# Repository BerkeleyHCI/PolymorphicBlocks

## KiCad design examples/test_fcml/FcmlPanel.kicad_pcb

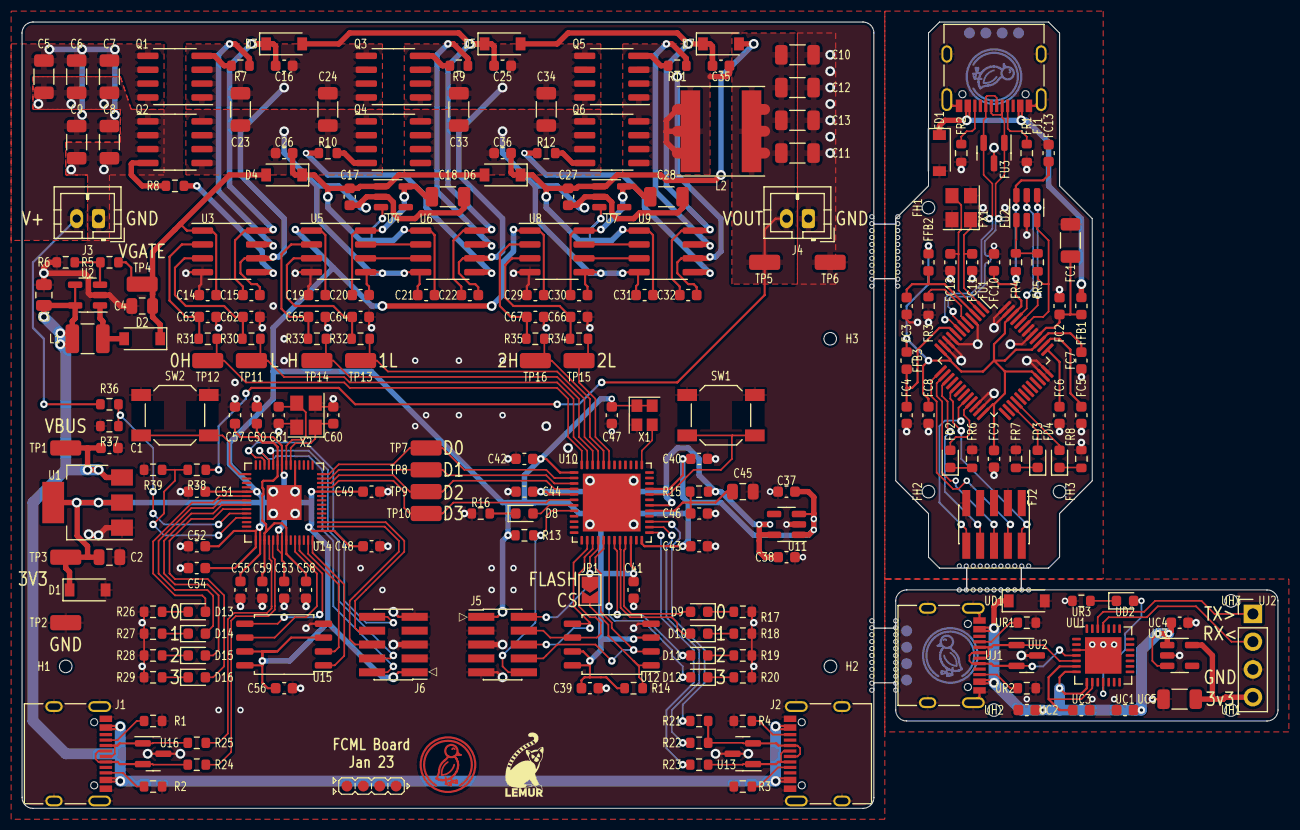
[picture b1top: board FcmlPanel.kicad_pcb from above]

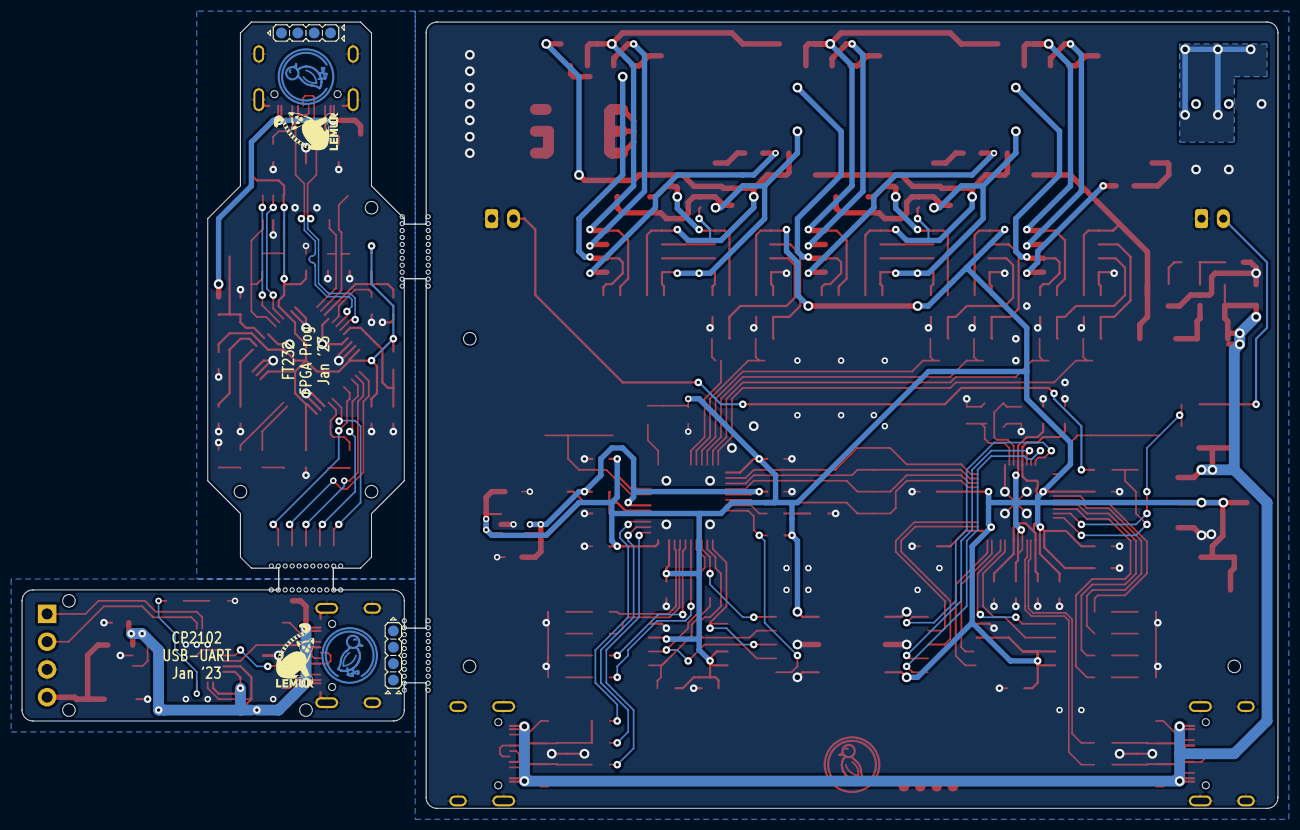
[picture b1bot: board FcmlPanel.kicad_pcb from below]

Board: 2 copper layers, 115.0 x 72.0 mm, 240 parts (6 on the bottom side), 108 nets.

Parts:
C1, C14, C15, C16, C17, C19, C20, C21, C22, C25, C26, C27, C29, C30, C31, C32, C35, C36, C37, C38, C39, C40, C41, C42, C43, C44, C46, C47, C48, C49, C50, C51, C52, C53, C54, C55, C56, C57, C58, C59, C60, C61, C62, C63, C64, C65, C66, C67: C_0603_1608Metric
C2, C3, C4, C45: C_0805_2012Metric
C5, C6, C7, C8, C9, C10, C11, C12, C13, C18, C23, C24, C28, C33, C34: C_1206_3216Metric
D1: BZT52C3V6 (SMC(Sangdest Microelectronicstronic (N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; D_SOD-123
D2: B0520W (Shikues) - 20V 390mV@500mA 500mA SOD-123 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; D_SOD-123
D3, D4, D5, D6, D7: B5819W SL (Changjiang Electronics Tech (CJ)) - 40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; D_SOD-123
D8, D9, D10, D11, D12, D13, D14, D15, D16: KT-0603R (Hubei KENTO Elec) - Red 615~630nm 1.9~2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; LED_0603_1608Metric
FC1: C_1206_3216Metric
FC2, FC3, FC4, FC5, FC6, FC7, FC8, FC9, FC10, FC11, FC12, FC13: C_0603_1608Metric
FD1: MMSZ5232A_R1_00001 (PANJIT International) - 5?A@3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; D_SOD-123
FD2: C2290 (Hubei KENTO Elec) - White 0603 Light Emitt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; LED_0603_1608Metric
FD3, FD4: LED_0603_1608Metric
FFB1, FFB2, FFB3: L_0603_1608Metric
FH1, FH2, FH3: JlcToolingHole_1.152mm
FJ1: COM-15111 (Sparkfun); USB_C_Receptacle_XKB_U262-16XN-4BVC11
FJ2: PinHeader1.27 Shrouded 2x5 (Generic); PinHeader_2x05_P1.27mm_Vertical_SMD
FR1, FR2, FR3, FR4, FR5, FR6, FR7, FR8: R_0603_1608Metric
FU1: FT232HL (FTDI, Future Technology Devices Internat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; LQFP-48_7x7mm_P0.5mm
FU2: 93LC56B (Microchip Technology); SOT-23-6
FU3: PGB102ST23 (Littelfuse); SOT-23
FU4: Duck; Symbol_Duckling
FU5: Lemur; Symbol_LemurSmall
FU6: IdDots4; Indicator_IdDots_4
FX1: Crystal_SMD_3225-4Pin_3.2x2.5mm
H1, H2, H3: JlcToolingHole_1.152mm
J1, J2: COM-15111 (Sparkfun); USB_C_Receptacle_XKB_U262-16XN-4BVC11
J3, J4: B2B-PH-K (JST); JST_PH_B2B-PH-K_1x02_P2.00mm_Vertical
J5, J6: PinHeader1.27 Shrouded 2x5 (Generic); PinHeader_2x05_P1.27mm_Vertical_SMD
JP1: SolderJumper-2_P1.3mm_Open_TrianglePad1.0x1.5mm
L1: L_1210_3225Metric
L2: L_Taiyo-Yuden_NR-80xx
Q1, Q2, Q3, Q4, Q5, Q6: HSM4410 (HUASHUO) - 30V 12A 2.5W 9.5m?@10V,12A 2.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; SOIC-8_3.9x4.9mm_P1.27mm
R1, R2, R3, R4, R5, R6, R7, R8, R9, R10, R11, R12, R13, R14, R15, R16, R17, R18, R19, R20, R21, R22, R23, R24, R25, R26, R27, R28, R29, R30, R31, R32, R33, R34, R35, R36, R37, R38, R39: R_0603_1608Metric
SW1, SW2: 5.1mm switch; SW_SPST_SKQG_WithoutStem
TP1: 5015 (Keystone) - vusb; TestPoint_TE_RCT_0805
TP2, TP6: 5015 (Keystone) - gnd; TestPoint_TE_RCT_0805
TP3: 5015 (Keystone) - v3v3; TestPoint_TE_RCT_0805
TP4: 5015 (Keystone) - vgate; TestPoint_TE_RCT_0805
TP5: 5015 (Keystone) - _conv_pwr_out_link; TestPoint_TE_RCT_0805
TP7: 5015 (Keystone) - _mcu_gpio_fpga0_link; TestPoint_TE_RCT_0805
TP8: 5015 (Keystone) - _mcu_gpio_fpga1_link; TestPoint_TE_RCT_0805
TP9: 5015 (Keystone) - _mcu_gpio_fpga2_link; TestPoint_TE_RCT_0805
TP10: 5015 (Keystone) - _mcu_gpio_fpga3_link; TestPoint_TE_RCT_0805
TP11: 5015 (Keystone) - _fpga_gpio_pwm_link.0L; TestPoint_TE_RCT_0805
TP12: 5015 (Keystone) - _fpga_gpio_pwm_link.0H; TestPoint_TE_RCT_0805
TP13: 5015 (Keystone) - _fpga_gpio_pwm_link.1L; TestPoint_TE_RCT_0805
TP14: 5015 (Keystone) - _fpga_gpio_pwm_link.1H; TestPoint_TE_RCT_0805
TP15: 5015 (Keystone) - _fpga_gpio_pwm_link.2L; TestPoint_TE_RCT_0805
TP16: 5015 (Keystone) - _fpga_gpio_pwm_link.2H; TestPoint_TE_RCT_0805
U1: LD1117S33TR (STMicroelectronics); SOT-223-3_TabPin2
U2: AP3012K (Diodes Incorporated); SOT-23-5
U3, U6, U9: IR2301 (Infineon Technologies); SOIC-8_3.9x4.9mm_P1.27mm
U4, U7: AP2204K-3.3 (Diodes Incorporated); SOT-23-5
U5, U8: CBMuD1200L (Corebai); SOIC-8_3.9x4.9mm_P1.27mm
U10: ICE40UP5K-SG48 (Lattice Semiconductor Corporation); QFN-48-1EP_7x7mm_P0.5mm_EP5.3x5.3mm
U11: LP5907MFX-1.2/NOPB (Texas Instruments); SOT-23-5
U12, U15: W25Q128JVSIQ (Winbond Electronics); SOIC-8_5.23x5.23mm_P1.27mm
U13, U16: PGB102ST23 (Littelfuse); SOT-23
U14: RP2040 (Raspberry Pi); QFN-56-1EP_7x7mm_P0.4mm_EP3.2x3.2mm
U17: Duck; Symbol_Duckling
U18: Lemur; Symbol_LemurSmall
U19: IdDots4; Indicator_IdDots_4
UC1, UC2, UC3, UC4: C_0603_1608Metric
UC5: C_1206_3216Metric
UD1: MMSZ5232A_R1_00001 (PANJIT International) - 5?A@3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; D_SOD-123
UD2: C2290 (Hubei KENTO Elec) - White 0603 Light Emitt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; LED_0603_1608Metric
UH1, UH2, UH3: JlcToolingHole_1.152mm
UJ1: COM-15111 (Sparkfun); USB_C_Receptacle_XKB_U262-16XN-4BVC11
UJ2: PinHeader2.54 1x4 (Generic); PinHeader_1x04_P2.54mm_Vertical
UR1, UR2, UR3: R_0603_1608Metric
UU1: CP2102 (Silicon Labs); QFN-28-1EP_5x5mm_P0.5mm_EP3.35x3.35mm
UU2: PGB102ST23 (Littelfuse); SOT-23
UU3: AP2204K-3.3 (Diodes Incorporated); SOT-23-5
UU4: Duck; Symbol_Duckling
UU5: Lemur; Symbol_LemurSmall
UU6: IdDots4; Indicator_IdDots_4
X1: Crystal_SMD_2520-4Pin_2.5x2.0mm
X2: Crystal_SMD_3225-4Pin_3.2x2.5mm

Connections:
cdone.res.a: D8.1, R16.1
conv.pwr_in: C5.1, C6.1, C7.1, C8.1, C9.1, J3.2, Q1.5, Q1.6, Q1.7, Q1.8, R36.1
conv.pwr_out: C10.1, C11.1, C12.1, C13.1, J4.2, L2.2, R38.1, TP5.1
conv.sw[0].high_boot_cap.pos: C15.1, C16.1, D3.1, U3.8
conv.sw[0].high_gate_res.a: R7.1, U3.7
conv.sw[0].high_gate_res.b: Q1.4, R7.2
conv.sw[0].low_gate_res.a: R8.1, U3.5
conv.sw[0].low_gate_res.b: Q2.4, R8.2
conv.sw[1].driver.high_in: U5.7, U6.2
conv.sw[1].driver.low_in: U5.6, U6.3
conv.sw[1].high_boot_out: C22.1, C25.1, D3.2, D5.1, U6.8
conv.sw[1].high_gate_res.a: R9.1, U6.7
conv.sw[1].high_gate_res.b: Q3.4, R9.2
conv.sw[1].high_in: C15.2, C16.2, C23.1, C24.1, Q1.1, Q1.2, Q1.3, Q3.5, Q3.6, Q3.7, Q3.8, U3.6
conv.sw[1].iso.pwr_b: C18.1, C20.1, U4.5, U5.8
conv.sw[1].low_gate_res.a: R10.1, U6.5
conv.sw[1].low_gate_res.b: Q4.4, R10.2
conv.sw[1].low_in: C17.2, C18.2, C20.2, C21.2, C23.2, C24.2, C26.2, Q2.5, Q2.6, Q2.7, Q2.8, Q4.1, Q4.2, Q4.3, U4.2, U5.5, U6.4
conv.sw[2].driver.high_in: U8.7, U9.2
conv.sw[2].driver.low_in: U8.6, U9.3
conv.sw[2].high_boot_out: C32.1, C35.1, D5.2, D7.1, U9.8
conv.sw[2].high_gate_res.a: R11.1, U9.7
conv.sw[2].high_gate_res.b: Q5.4, R11.2
conv.sw[2].high_in: C22.2, C25.2, C33.1, C34.1, Q3.1, Q3.2, Q3.3, Q5.5, Q5.6, Q5.7, Q5.8, U6.6
conv.sw[2].iso.pwr_b: C28.1, C30.1, U7.5, U8.8
conv.sw[2].low_boot_in: C17.1, C21.1, C26.1, D4.1, D6.2, U4.1, U4.3, U6.1
conv.sw[2].low_boot_out: C27.1, C31.1, C36.1, D6.1, D7.2, U7.1, U7.3, U9.1
conv.sw[2].low_gate_res.a: R12.1, U9.5
conv.sw[2].low_gate_res.b: Q6.4, R12.2
conv.sw[2].low_in: C27.2, C28.2, C30.2, C31.2, C33.2, C34.2, C36.2, Q4.5, Q4.6, Q4.7, Q4.8, Q6.1, Q6.2, Q6.3, U7.2, U8.5, U9.4
conv.sw[2].low_out: C32.2, C35.2, L2.1, Q5.1, Q5.2, Q5.3, Q6.5, Q6.6, Q6.7, Q6.8, U9.6
conv_in_sense.output: R36.2, R37.1, U14.38
conv_out_sense.output: R38.2, R39.1, U14.39
fpga.cdone: D8.2, U10.7
fpga.cs_jmp.output: JP1.2, R14.2, U12.1
fpga.gpio.led_0: D9.2, U10.21
fpga.gpio.led_1: D10.2, U10.20
fpga.gpio.led_2: D11.2, U10.19
fpga.gpio.led_3: D12.2, U10.18
fpga.gpio.pwm_0H: R31.1, TP12.1, U10.48
fpga.gpio.pwm_0L: R30.1, TP11.1, U10.47
fpga.gpio.pwm_1H: R33.1, TP14.1, U10.46
fpga.gpio.pwm_1L: R32.1, TP13.1, U10.45
fpga.gpio.pwm_2H: R35.1, TP16.1, U10.44
fpga.gpio.pwm_2L: R34.1, TP15.1, U10.43
fpga.ic.creset_b: J5.10, R13.2, U10.8
fpga.ic.spi_config.miso: J5.8, U10.17, U12.2
fpga.ic.spi_config.mosi: J5.6, U10.14, U12.5
fpga.ic.spi_config.sck: J5.4, U10.15, U12.6
fpga.ic.spi_config_cs: J5.2, JP1.1, U10.16
fpga.pll_res.pwr_out: C45.1, C46.1, R15.2, U10.29
fpga.vcc_reg.pwr_out: C38.1, C44.1, R15.1, U10.5, U10.30, U11.5
fpga_led.led[0].res.a: D9.1, R17.1
fpga_led.led[1].res.a: D10.1, R18.1
fpga_led.led[2].res.a: D11.1, R19.1
fpga_led.led[3].res.a: D12.1, R20.1
fpga_osc.out: U10.37, X1.3
fpga_sw.out: SW1.2, U10.32
gnd: C1.2, C2.2, C3.2, C4.2, C5.2, C6.2, C7.2, C8.2, C9.2, C10.2, C11.2, C12.2, C13.2, C14.2, C19.2, C29.2, C37.2, C38.2, C39.2, C40.2, C41.2, C42.2, C43.2, C44.2, C45.2, C46.2, C47.2, C48.2, C49.2, C50.2, C51.2, C52.2, C53.2, C54.2, C55.2, C56.2, C57.2, C58.2, C59.2, C60.2, C61.2, C62.2, C63.2, C64.2, C65.2, C66.2, C67.2, D1.2, FC1.2, FC2.2, FC3.2, FC4.2, FC5.2, FC6.2, FC7.2, FC8.2, FC9.2, FC10.2, FC11.2, FC12.2, FC13.2, FD1.2, FJ1.A1, FJ1.A12, FJ1.B1, FJ1.B12, FJ1.S1, FJ2.3, FJ2.5, FJ2.9, FR1.1, FR2.1, FR3.2, FR6.2, FR7.2, FR8.2, FU1.4, FU1.9, FU1.10, FU1.11, FU1.22, FU1.23, FU1.35, FU1.36, FU1.41, FU1.42, FU1.47, FU1.48, FU2.2, FU3.3, FX1.2, FX1.4, J1.A1, J1.A12, J1.B1, J1.B12, J1.S1, J2.A1, J2.A12, J2.B1, J2.B12, J2.S1, J3.1, J4.1, J5.3, J5.5, J5.9, J6.3, J6.5, J6.9, Q2.1, Q2.2, Q2.3, R1.1, R2.1, R3.1, R4.1, R6.2, R16.2, R17.2, R18.2, R19.2, R20.2, R26.2, R27.2, R28.2, R29.2, R37.2, R39.2, SW1.1, SW2.1, TP2.1, TP6.1, U1.1, U2.2, U3.4, U5.4, U8.4, U10.49, U11.2, U12.4, U13.3, U14.19, U14.57, U15.4, U16.3, UC1.2, UC2.2, UC3.2, UC4.2, UC5.2, UD1.2, UJ1.A1, UJ1.A12, UJ1.B1, UJ1.B12, UJ1.S1, UJ2.3, UR1.1, UR2.1, UR3.2, UU1.3, UU1.29, UU2.3, UU3.2, X1.2, X2.2, X2.4
mcu.crystal.crystal.a: C60.1, U14.20, X2.1
mcu.crystal.crystal.b: C61.1, U14.21, X2.3
mcu.gpio.led_0: D13.2, U14.34
mcu.gpio.led_1: D14.2, U14.35
mcu.gpio.led_2: D15.2, U14.36
mcu.gpio.led_3: D16.2, U14.37
mcu.ic.qspi.miso: U14.55, U15.2
mcu.ic.qspi.mosi: U14.53, U15.5
mcu.ic.qspi.sck: U14.52, U15.6
mcu.ic.qspi_cs: U14.56, U15.1
mcu.ic.vreg_vout: C57.1, C58.1, C59.1, U14.23, U14.45, U14.50
mcu.swd.swd.reset: J6.10, U14.26
mcu.swd.swd.swclk: J6.4, U14.24
mcu.swd.swd.swdio: J6.2, U14.25
mcu.swd.swo: J6.6, U14.2
mcu.swd.tdi: J6.8, U14.3
mcu.usb_chain_0.d_N: R25.1, U14.46
mcu.usb_chain_0.d_P: R24.1, U14.47
mcu_leds.led[0].res.a: D13.1, R26.1
mcu_leds.led[1].res.a: D14.1, R27.1
mcu_leds.led[2].res.a: D15.1, R28.1
mcu_leds.led[3].res.a: D16.1, R29.1
mcu_sw.out: SW2.2, U14.29
reg_vgate.fb.output: R5.2, R6.1, U2.3
reg_vgate.power_path.switch: D2.2, L1.2, U2.1
tp_fpga[0].io: TP7.1, U10.2, U14.14
tp_fpga[1].io: TP8.1, U10.3, U14.13
tp_fpga[2].io: TP9.1, U10.4, U14.12
tp_fpga[3].io: TP10.1, U10.6, U14.11
tp_pwm.output.0H: C63.1, R31.2, U3.2
tp_pwm.output.0L: C62.1, R30.2, U3.3
tp_pwm.output.1H: C65.1, R33.2, U5.2
tp_pwm.output.1L: C64.1, R32.2, U5.3
tp_pwm.output.2H: C67.1, R35.2, U8.2
tp_pwm.output.2L: C66.1, R34.2, U8.3
usb_fpga.conn.A5: J2.A5, R3.2
usb_fpga.conn.B5: J2.B5, R4.2
usb_fpga_bitbang.dm: R23.1, U10.25
usb_fpga_bitbang.dp: R22.1, U10.26
usb_fpga_bitbang.dp_pull: R21.1, U10.27
usb_fpga_chain_0.d_N: J2.A7, J2.B7, R23.2, U13.1
usb_fpga_chain_0.d_P: J2.A6, J2.B6, R21.2, R22.2, U13.2
usb_mcu.conn.A5: J1.A5, R1.2
usb_mcu.conn.B5: J1.B5, R2.2
usb_mcu_chain_0.d_N: J1.A7, J1.B7, R25.2, U16.1
usb_mcu_chain_0.d_P: J1.A6, J1.B6, R24.2, U16.2
v3v3: C2.1, C19.1, C29.1, C37.1, C39.1, C40.1, C41.1, C42.1, C43.1, C47.1, C48.1, C49.1, C50.1, C51.1, C52.1, C53.1, C54.1, C55.1, C56.1, D1.1, J5.1, J6.1, R13.1, R14.1, TP3.1, U1.2, U5.1, U8.1, U10.1, U10.22, U10.24, U10.33, U11.1, U11.3, U12.3, U12.7, U12.8, U14.1, U14.10, U14.22, U14.33, U14.42, U14.43, U14.44, U14.48, U14.49, U15.3, U15.7, U15.8, UC5.1, UJ2.4, UU3.5, X1.1, X1.4
vgate: C4.1, C14.1, D2.1, D4.2, R5.1, TP4.1, U3.1
vusb: C1.1, C3.1, FD1.1, FFB1.1, FJ1.A4, FJ1.A9, FJ1.B4, FJ1.B9, J1.A4, J1.A9, J1.B4, J1.B9, J2.A4, J2.A9, J2.B4, J2.B9, L1.1, TP1.1, U1.3, U2.4, U2.5, UC1.1, UC2.1, UC4.1, UD1.1, UJ1.A4, UJ1.A9, UJ1.B4, UJ1.B9, UU1.7, UU1.8, UU3.1, UU3.3

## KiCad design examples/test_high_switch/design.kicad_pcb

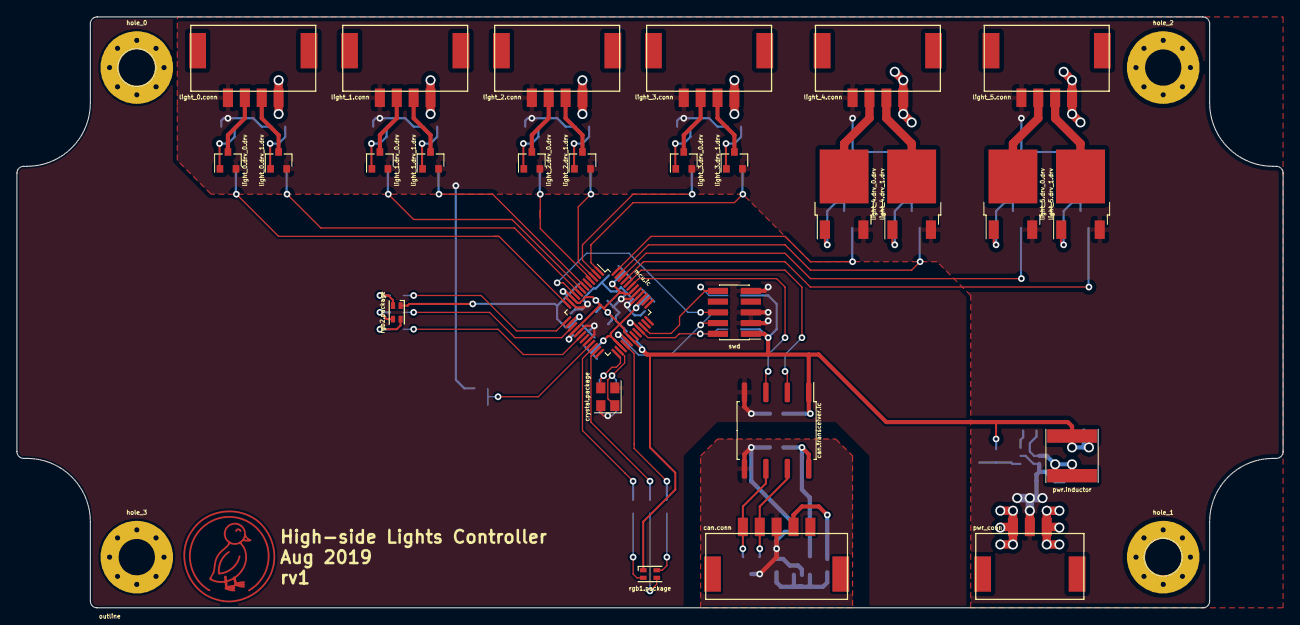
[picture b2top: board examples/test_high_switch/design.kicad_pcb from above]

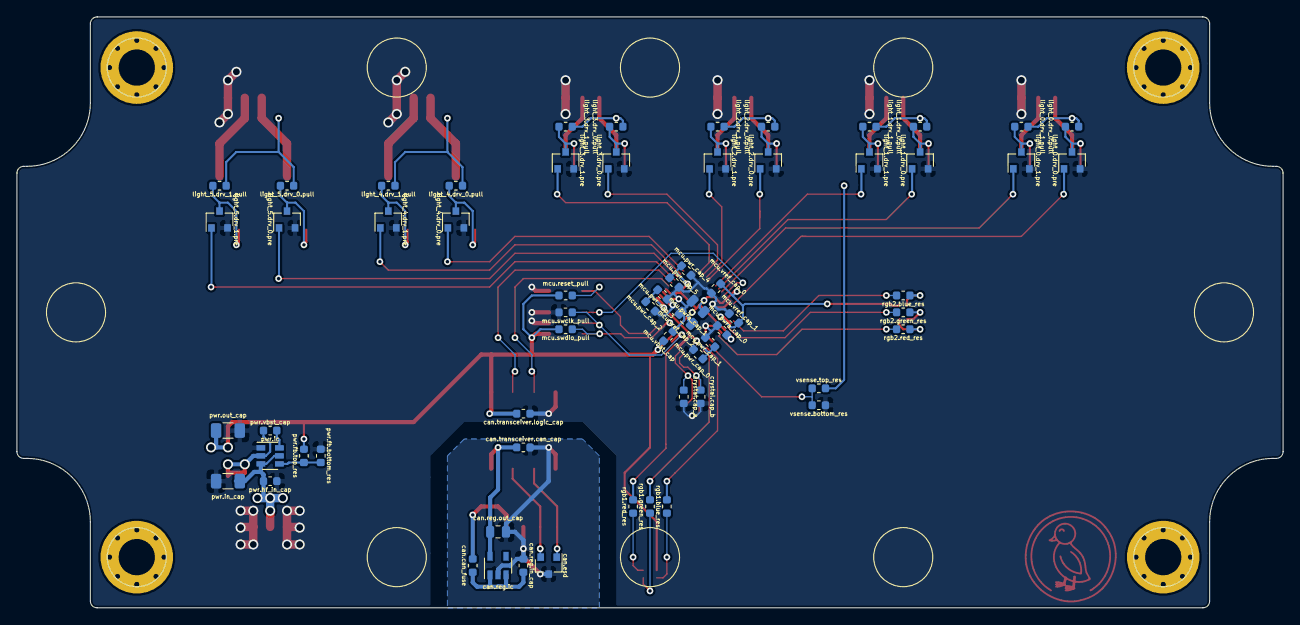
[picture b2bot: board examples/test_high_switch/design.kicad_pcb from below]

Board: 2 copper layers, 150.0 x 70.0 mm, 96 parts (63 on the bottom side), 69 nets.

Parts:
can.can_fuse: 0ZCM0005FF2G; R_0603_1608Metric
can.conn: Duraclik; Molex_DuraClik_vert_5pin
can.esd: PESD1CAN,215; SOT-23
can.reg.ic: AP2204K-5.0; SOT-23-5
can.reg.in_cap: 1µF, 25V, CL10A105KA8NNNC (C=(8.8e-07, 1.32e-06) 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; C_0603_1608Metric
can.reg.out_cap: 2.2µF, 10V, CL21B225KPFNNNE (C=(1.76e-06, 2.64e-0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; C_0805_2012Metric
can.transceiver.can_cap, can.transceiver.logic_cap: 0.1µF, 50V, CL10B104KB8NNNC (C=(8e-08, 1.2e-07) F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; C_0603_1608Metric
can.transceiver.ic: ISO1050DUB; SOP-8_6.62x9.15mm_P2.54mm
crystal.cap_a, crystal.cap_b: 18pF, 50V, CL10C180FB8NNNC (C=(1.764e-11, 1.836e-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; C_0603_1608Metric
crystal.package: 7V-12.000MAHE-T; Oscillator_SMD_Abracon_ASE-4Pin_3.2x2.5mm
duck: Duck; Duckling
hole_0, hole_1, hole_2, hole_3: M4; MountingHole_4.3mm_M4_Pad_Via
light_0.conn, light_1.conn, light_2.conn, light_3.conn, light_4.conn, light_5.conn: Duraclik; Molex_DuraClik_vert_4pin
light_0.drv_0.drv, light_0.drv_1.drv, light_1.drv_0.drv, light_1.drv_1.drv, light_2.drv_0.drv, light_2.drv_1.drv, light_3.drv_0.drv, light_3.drv_1.drv: DMP3099L-7 (Vds=(10.8, 13.200000000000001) V, Ids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; SOT-23
light_0.drv_0.pre, light_0.drv_1.pre, light_1.drv_0.pre, light_1.drv_1.pre, light_2.drv_0.pre, light_2.drv_1.pre, light_3.drv_0.pre, light_3.drv_1.pre, light_4.drv_0.pre, light_4.drv_1.pre, light_5.drv_0.pre, light_5.drv_1.pre: NX138AKR (Vds=(10.8, 13.200000000000001) V, Ids=(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; SOT-23
light_0.drv_0.pull, light_0.drv_1.pull, light_1.drv_0.pull, light_1.drv_1.pull, light_2.drv_0.pull, light_2.drv_1.pull, light_3.drv_0.pull, light_3.drv_1.pull, light_4.drv_0.pull, light_4.drv_1.pull, light_5.drv_0.pull, light_5.drv_1.pull: 10000, 1%, 0.1W (R=(9900.0, 10100.0) Ohm, P=(0.0,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; R_0603_1608Metric
light_4.drv_0.drv, light_4.drv_1.drv, light_5.drv_0.drv, light_5.drv_1.drv: TSM7P06CP ROG (Vds=(10.8, 13.200000000000001) V, 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; TO-252-2
mcu.ic: LPC1549JBD48; LQFP-48_7x7mm_P0.5mm
mcu.pwr_cap_0, mcu.pwr_cap_2, mcu.pwr_cap_4, mcu.pwra_cap_0, mcu.vbat_cap, mcu.vref_cap_0, mcu.vref_cap_1: 0.1µF, 50V, CL10B104KB8NNNC (C=(8e-08, 1.2e-07) F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; C_0603_1608Metric
mcu.pwr_cap_1, mcu.pwr_cap_3, mcu.pwr_cap_5: 10000pF, 50V, CL10B103KB8NNNC (C=(8e-09, 1.2e-08)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; C_0603_1608Metric
mcu.pwra_cap_1, mcu.vref_cap_2: 10µF, 10V, CL21A106KPFNNNG (C=(8e-06, 1.199999999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; C_0805_2012Metric
mcu.reset_pull: 10000, 1%, 0.1W (R=(9500.0, 10500.0) Ohm, P=(0.0,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; R_0603_1608Metric
mcu.swclk_pull, mcu.swdio_pull: 10000, 1%, 0.1W (R=(9500.0, 105000.0) Ohm, P=(0.0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; R_0603_1608Metric
outline: PN1332_Panel; Outline_150mm_70mm_PNX-91432
pwr.fb.bottom_res: 10000, 1%, 0.1W (R=(9900.0, 10100.0) Ohm, P=(0.0,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; R_0603_1608Metric
pwr.fb.top_res: 33000, 1%, 0.1W (R=(32670.0, 33330.0) Ohm, P=(0.0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; R_0603_1608Metric
pwr.hf_in_cap, pwr.vbst_cap: 0.1µF, 50V, CL10B104KB8NNNC (C=(8e-08, 1.2e-07) F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; C_0603_1608Metric
pwr.ic: TPS561201; SOT-23-6
pwr.in_cap: 22µF, 16V, CL31A226MOCLNNC (C=(7.498403575989784e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; C_1206_3216Metric
pwr.inductor: 10µH, 2.5A, NR6045T100M (L=(4.6396372126436784e-0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; L_Taiyo-Yuden_NR-60xx
pwr.out_cap: 22µF, 6.3V, CL31A226MQHNNNE (C=(1.034482758620689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; C_1206_3216Metric
pwr_conn: Duraclik; Molex_DuraClik_vert_3pin
rgb1.blue_res, rgb1.green_res, rgb1.red_res, rgb2.blue_res, rgb2.green_res, rgb2.red_res: 1000, 1%, 0.1W (R=(950.0, 1050.0) Ohm, P=(0.0, 0.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; R_0603_1608Metric
rgb1.package, rgb2.package: LED_RGB_0606
swd: SWD; PinHeader_2x05_P1.27mm_Vertical_SMD
vsense.bottom_res: 1500, 1%, 0.1W (R=(1485.0, 1515.0) Ohm, P=(0.0, 0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; R_0603_1608Metric
vsense.top_res: 4700, 1%, 0.1W (R=(4653.0, 4747.0) Ohm, P=(0.0, 0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; R_0603_1608Metric

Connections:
can.can.canh: can.conn.4, can.esd.2, can.transceiver.ic.7
can.can.canl: can.conn.5, can.esd.1, can.transceiver.ic.6
can.can_gnd: can.conn.3, can.esd.3, can.reg.ic.2, can.reg.in_cap.2, can.reg.out_cap.2, can.transceiver.can_cap.2, can.transceiver.ic.5
can.can_pwr: can.can_fuse.1, can.conn.2
can.controller.txd: can.transceiver.ic.3, mcu.ic.43
can.reg.pwr_in: can.can_fuse.2, can.reg.ic.1, can.reg.ic.3, can.reg.in_cap.1
can.reg.pwr_out: can.reg.ic.5, can.reg.out_cap.1, can.transceiver.can_cap.1, can.transceiver.ic.8
crystal.crystal.b: crystal.cap_b.1, crystal.package.3, mcu.ic.25
gnd: can.transceiver.ic.4, can.transceiver.logic_cap.2, crystal.cap_a.2, crystal.cap_b.2, crystal.package.2, crystal.package.4, light_0.conn.4, light_0.drv_0.pre.2, light_0.drv_1.pre.2, light_1.conn.4, light_1.drv_0.pre.2, light_1.drv_1.pre.2, light_2.conn.4, light_2.drv_0.pre.2, light_2.drv_1.pre.2, light_3.conn.4, light_3.drv_0.pre.2, light_3.drv_1.pre.2, light_4.conn.4, light_4.drv_0.pre.2, light_4.drv_1.pre.2, light_5.conn.4, light_5.drv_0.pre.2, light_5.drv_1.pre.2, mcu.ic.11, mcu.ic.17, mcu.ic.20, mcu.ic.40, mcu.ic.41, mcu.pwr_cap_0.2, mcu.pwr_cap_1.2, mcu.pwr_cap_2.2, mcu.pwr_cap_3.2, mcu.pwr_cap_4.2, mcu.pwr_cap_5.2, mcu.pwra_cap_0.2, mcu.pwra_cap_1.2, mcu.swclk_pull.1, mcu.vbat_cap.2, mcu.vref_cap_0.2, mcu.vref_cap_1.2, mcu.vref_cap_2.2, pwr.fb.bottom_res.2, pwr.hf_in_cap.2, pwr.ic.1, pwr.in_cap.2, pwr.out_cap.2, pwr_conn.1, pwr_conn.3, swd.3, swd.5, swd.9, vsense.bottom_res.2
light_0.conn.out_0: light_0.conn.2, light_0.drv_0.drv.3
light_0.control_0: light_0.drv_0.pre.1, mcu.ic.12
light_0.drv_0.drv.gate: light_0.drv_0.drv.1, light_0.drv_0.pre.3, light_0.drv_0.pull.2
light_0.drv_1.output: light_0.conn.3, light_0.drv_1.drv.3
light_0.drv_1.pull.2: light_0.drv_1.drv.1, light_0.drv_1.pre.3, light_0.drv_1.pull.2
light_1.conn.out_0: light_1.conn.2, light_1.drv_0.drv.3
light_1.conn.out_1: light_1.conn.3, light_1.drv_1.drv.3
light_1.control_0: light_1.drv_0.pre.1, mcu.ic.7
light_1.drv_0.drv.gate: light_1.drv_0.drv.1, light_1.drv_0.pre.3, light_1.drv_0.pull.2
light_1.drv_1.drv.1: light_1.drv_1.drv.1, light_1.drv_1.pre.3, light_1.drv_1.pull.2
light_2.conn.out_1: light_2.conn.3, light_2.drv_1.drv.3
light_2.control_1: light_2.drv_1.pre.1, mcu.ic.3
light_2.drv_0.output: light_2.conn.2, light_2.drv_0.drv.3
light_2.drv_0.pull.2: light_2.drv_0.drv.1, light_2.drv_0.pre.3, light_2.drv_0.pull.2
light_2.drv_1.drv.gate: light_2.drv_1.drv.1, light_2.drv_1.pre.3, light_2.drv_1.pull.2
light_3.conn.3: light_3.conn.3, light_3.drv_1.drv.3
light_3.drv_0.output: light_3.conn.2, light_3.drv_0.drv.3
light_3.drv_0.pre.drain: light_3.drv_0.drv.1, light_3.drv_0.pre.3, light_3.drv_0.pull.2
light_3.drv_1.drv.1: light_3.drv_1.drv.1, light_3.drv_1.pre.3, light_3.drv_1.pull.2
light_4.conn.out_1: light_4.conn.3, light_4.drv_1.drv.2
light_4.control_0: light_4.drv_0.pre.1, mcu.ic.48
light_4.drv_0.drv.gate: light_4.drv_0.drv.1, light_4.drv_0.pre.3, light_4.drv_0.pull.2
light_4.drv_0.output: light_4.conn.2, light_4.drv_0.drv.2
light_4.drv_1.drv.1: light_4.drv_1.drv.1, light_4.drv_1.pre.3, light_4.drv_1.pull.2
light_5.conn.2: light_5.conn.2, light_5.drv_0.drv.2
light_5.conn.out_1: light_5.conn.3, light_5.drv_1.drv.2
light_5.control_0: light_5.drv_0.pre.1, mcu.ic.46
light_5.control_1: light_5.drv_1.pre.1, mcu.ic.45
light_5.drv_0.pull.b: light_5.drv_0.drv.1, light_5.drv_0.pre.3, light_5.drv_0.pull.2
light_5.drv_1.pre.3: light_5.drv_1.drv.1, light_5.drv_1.pre.3, light_5.drv_1.pull.2
mcu.can_0.rxd: can.transceiver.ic.2, mcu.ic.44
mcu.digital_4: light_4.drv_1.pre.1, mcu.ic.47
mcu.digital_6: light_3.drv_1.pre.1, mcu.ic.1
mcu.digital_7: light_3.drv_0.pre.1, mcu.ic.2
mcu.digital_9: light_2.drv_0.pre.1, mcu.ic.4
mcu.digital_10: light_1.drv_1.pre.1, mcu.ic.6
mcu.digital_12: light_0.drv_1.pre.1, mcu.ic.8
mcu.digital_15: mcu.ic.15, rgb2.green_res.2
mcu.digital_16: mcu.ic.18, rgb2.red_res.2
mcu.digital_18: mcu.ic.23, rgb1.green_res.2
mcu.xtal.xtal_in: crystal.cap_a.1, crystal.package.1, mcu.ic.26
pwr.ic.4: pwr.fb.bottom_res.1, pwr.fb.top_res.2, pwr.ic.4
pwr.sw: pwr.ic.2, pwr.inductor.1, pwr.vbst_cap.2
pwr.vbst_cap.1: pwr.ic.6, pwr.vbst_cap.1
rgb1.blue: mcu.ic.22, rgb1.blue_res.2
rgb1.blue_res.a: rgb1.blue_res.1, rgb1.package.2
rgb1.package.3: rgb1.green_res.1, rgb1.package.3
rgb1.package.4: rgb1.package.4, rgb1.red_res.1
rgb1.red: mcu.ic.28, rgb1.red_res.2
rgb2.blue: mcu.ic.13, rgb2.blue_res.2
rgb2.blue_res.a: rgb2.blue_res.1, rgb2.package.2
rgb2.package.3: rgb2.green_res.1, rgb2.package.3
rgb2.package.4: rgb2.package.4, rgb2.red_res.1
swd.2: mcu.ic.33, mcu.swdio_pull.2, swd.2
swd.4: mcu.ic.29, mcu.swclk_pull.2, swd.4
swd.6: mcu.ic.9, swd.6
swd.10: mcu.ic.34, mcu.reset_pull.2, swd.10
v3v3: can.transceiver.ic.1, can.transceiver.logic_cap.1, mcu.ic.10, mcu.ic.14, mcu.ic.16, mcu.ic.27, mcu.ic.30, mcu.ic.39, mcu.ic.42, mcu.pwr_cap_0.1, mcu.pwr_cap_1.1, mcu.pwr_cap_2.1, mcu.pwr_cap_3.1, mcu.pwr_cap_4.1, mcu.pwr_cap_5.1, mcu.pwra_cap_0.1, mcu.pwra_cap_1.1, mcu.reset_pull.1, mcu.swdio_pull.1, mcu.vbat_cap.1, mcu.vref_cap_0.1, mcu.vref_cap_1.1, mcu.vref_cap_2.1, pwr.fb.top_res.1, pwr.inductor.2, pwr.out_cap.1, rgb1.package.1, rgb2.package.1, swd.1
vin: light_0.conn.1, light_0.drv_0.drv.2, light_0.drv_0.pull.1, light_0.drv_1.drv.2, light_0.drv_1.pull.1, light_1.conn.1, light_1.drv_0.drv.2, light_1.drv_0.pull.1, light_1.drv_1.drv.2, light_1.drv_1.pull.1, light_2.conn.1, light_2.drv_0.drv.2, light_2.drv_0.pull.1, light_2.drv_1.drv.2, light_2.drv_1.pull.1, light_3.conn.1, light_3.drv_0.drv.2, light_3.drv_0.pull.1, light_3.drv_1.drv.2, light_3.drv_1.pull.1, light_4.conn.1, light_4.drv_0.drv.3, light_4.drv_0.pull.1, light_4.drv_1.drv.3, light_4.drv_1.pull.1, light_5.conn.1, light_5.drv_0.drv.3, light_5.drv_0.pull.1, light_5.drv_1.drv.3, light_5.drv_1.pull.1, pwr.hf_in_cap.1, pwr.ic.3, pwr.ic.5, pwr.in_cap.1, pwr_conn.2, vsense.top_res.1
vsense.out: mcu.ic.21, vsense.bottom_res.1, vsense.top_res.2

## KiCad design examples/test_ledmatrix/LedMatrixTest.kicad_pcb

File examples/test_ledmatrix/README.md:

## Revision 1

Revision 1 of this board had an error, where the ESP32-C3's IO8 was pulled down instead of up.
This prevents the device from going into download mode.

Suggested fix: remove the pull-down resistor, then bridge the IO8-side resistor pad to the adjacent EN resistor pad, which is pulled up.

This has since been fixed in the ESP32-C3 definition, though that fix is currently untested.

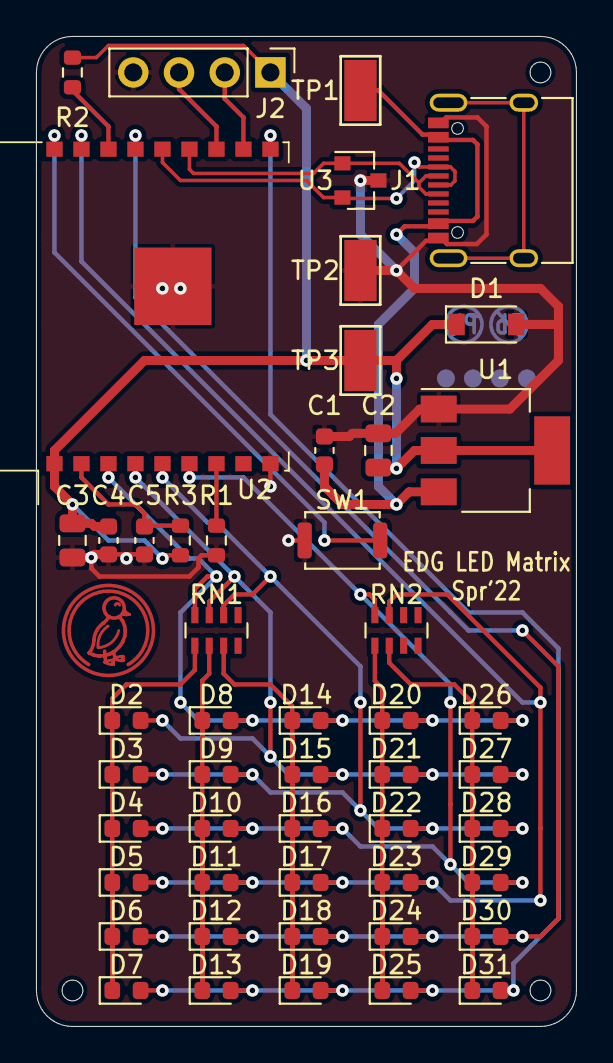
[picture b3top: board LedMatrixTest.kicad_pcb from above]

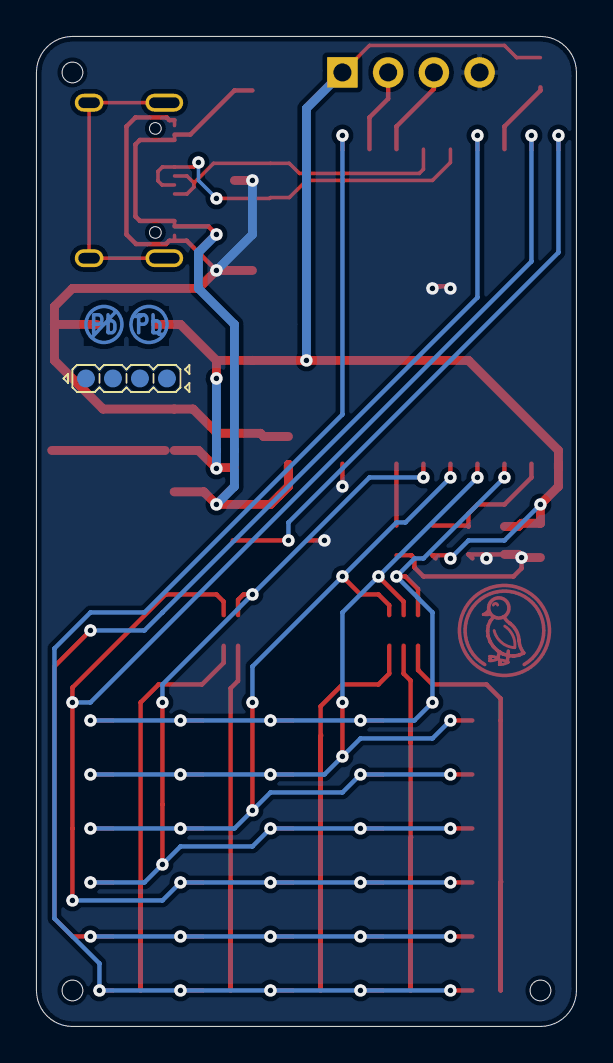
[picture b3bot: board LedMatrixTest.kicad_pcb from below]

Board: 2 copper layers, 30.0 x 55.0 mm, 56 parts (2 on the bottom side), 23 nets.

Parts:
1: Indicator_LeadFree
2: Indicator_IdDots_4
C1, C4: C14663; C_0603_1608Metric
C2: C1779; C_0805_2012Metric
C3: C15850; C_0805_2012Metric
C5: C15849; C_0603_1608Metric
D1: C499796; D_SOD-123
D2, D3, D4, D5, D6, D7, D8, D9, D10, D11, D12, D13, D14, D15, D16, D17, D18, D19, D20, D21, D22, D23, D24, D25, D26, D27, D28, D29, D30, D31: C72038; LED_0603_1608Metric
H1, H2, H3: JlcToolingHole_1.152mm
J1: C165948; USB_C_Receptacle_XKB_U262-16XN-4BVC11
J2: PinHeader_1x04_P2.54mm_Vertical
R1, R2, R3: C25804; R_0603_1608Metric
RN1, RN2: C425057; R_Array_Concave_4x0603
SW1: SW_Push_SPST_NO_Alps_SKRK
TP1, TP2, TP3: C238130; TestPoint_Keystone_5015_Micro-Minature
U1: C86781; SOT-223-3_TabPin2
U2: C2934560; ESP-WROOM-02
U3: C87911; SOT-23
U4: Symbol_Duckling

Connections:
gnd: C1.2, C2.2, C3.2, C4.2, C5.2, D1.2, J1.A1, J1.A12, J1.B1, J1.B12, J2.4, R1.1, SW1.1, TP2.1, U1.1, U2.9, U2.19, U3.3
matrix.ios.5: D6.2, D12.2, D18.2, D24.2, D30.2, U2.15
matrix.ios.6: D7.2, D13.2, D19.2, D25.2, D31.2, U2.10
matrix_res1.a.0: D2.1, D3.1, D4.1, D5.1, D6.1, D7.1, RN1.1
matrix_res1.a.1: D8.1, D9.1, D10.1, D11.1, D12.1, D13.1, RN1.2
matrix_res1.a.2: D14.1, D15.1, D16.1, D17.1, D18.1, D19.1, RN1.3
matrix_res1.b.1: D2.2, D15.2, D21.2, D27.2, RN1.7, U2.4
matrix_res2.a.0: D20.1, D21.1, D22.1, D23.1, D24.1, D25.1, RN2.1
matrix_res2.a.1: D26.1, D27.1, D28.1, D29.1, D30.1, D31.1, RN2.2
mcu.en_pull.output: C5.1, R3.2, U2.2
mcu.gpio.led_0: D8.2, D14.2, D20.2, D26.2, RN1.8, U2.3
mcu.gpio.led_2: D3.2, D9.2, D22.2, D28.2, RN1.6, U2.5
mcu.gpio.led_3: D4.2, D10.2, D16.2, D29.2, RN2.8, U2.6
mcu.gpio.led_4: D5.2, D11.2, D17.2, D23.2, RN2.7, U2.17
mcu.gpio.sw1: SW1.2, U2.18
mcu.ic.uart0.rx: J2.2, U2.11
mcu.io2_pull.io: R2.2, U2.16
mcu.io8_pull.b: R1.2, U2.7
mcu.uart0.uart.rx: J2.3, U2.12
usb.usb.dp: J1.A6, J1.B6, U2.14, U3.2
usb_esd.usb.dm: J1.A7, J1.B7, U2.13, U3.1
v3v3: C2.1, C3.1, C4.1, D1.1, J2.1, R2.1, R3.1, TP3.1, U1.2, U2.1
vusb: C1.1, J1.A4, J1.A9, J1.B4, J1.B9, TP1.1, U1.3
